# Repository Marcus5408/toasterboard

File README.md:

# Toasterboard

A very scuffed attempt at recreating a Breadboard Companion.

Made for the Hardware workshop led by Acon at [Hack Club Juice](juice.hackclub.com) utilizing a electronics kit from [Hack Club Solder](solder.hackclub.com).

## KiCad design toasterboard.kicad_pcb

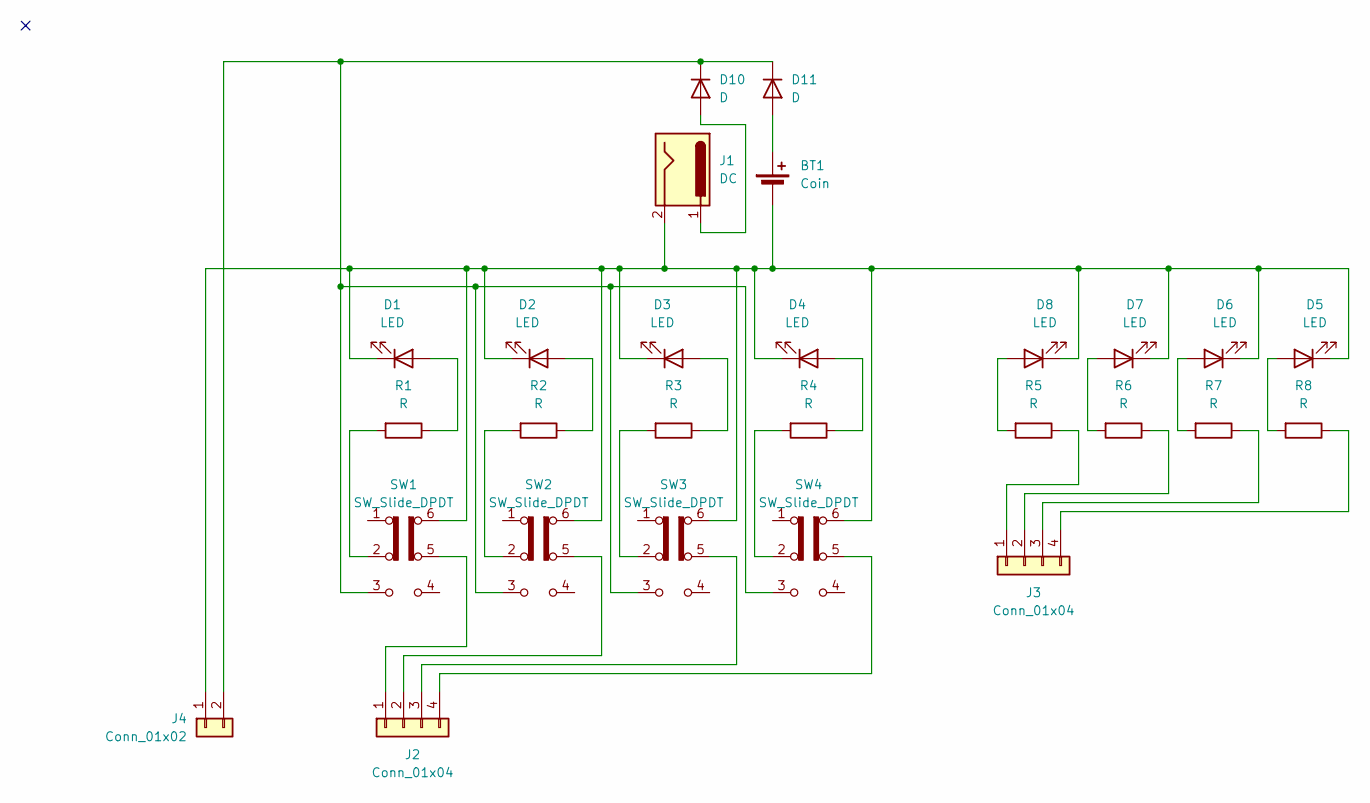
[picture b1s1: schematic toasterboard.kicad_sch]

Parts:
BT1: Coin; BatteryHolder_Keystone_3034_1x20mm
D1, D2, D3, D4, D5, D6, D7, D8: LED; LED_D5.0mm
D10, D11: D; D_DO-35_SOD27_P7.62mm_Horizontal
J1: DC; BarrelJack_CLIFF_FC681465S_SMT_Horizontal
J2, J3: Conn_01x04; PinHeader_1x04_P1.00mm_Vertical
J4: Conn_01x02; PinHeader_1x02_P1.00mm_Vertical
R1, R2, R3, R4, R5, R6, R7, R8: R; R_Axial_DIN0207_L6.3mm_D2.5mm_P7.62mm_Horizontal
SW1, SW2, SW3, SW4: SW_Slide_DPDT; SW_E-Switch_EG1271_SPDT

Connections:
unnamed: BT1.1 (+), D11.2 (A)
unnamed: BT1.2 (-), D1.1 (K), D2.1 (K), D3.1 (K), D4.1 (K), D5.1 (K), D6.1 (K), D7.1 (K), D8.1 (K), J1.2, J4.1, SW1.6 (C), SW2.6 (C), SW3.6 (C), SW4.6 (C)
unnamed: D1.2 (A), R1.1
unnamed: D2.2 (A), R2.1
unnamed: D3.2 (A), R3.1
unnamed: D4.2 (A), R4.1
unnamed: D5.2 (A), R8.2
unnamed: D6.2 (A), R7.2
unnamed: D7.2 (A), R6.2
unnamed: D8.2 (A), R5.2
unnamed: D10.2 (A), J1.1
unnamed: D10.1 (K), D11.1 (K), J4.2, SW1.3 (C), SW2.3 (C), SW3.3 (C), SW4.3 (C)
unnamed: J2.1, SW1.5 (B)
unnamed: J2.2, SW2.5 (B)
unnamed: J2.3, SW3.5 (B)
unnamed: J2.4, SW4.5 (B)
unnamed: J3.1, R5.1
unnamed: J3.2, R6.1
unnamed: J3.3, R7.1
unnamed: J3.4, R8.1
unnamed: R1.2, SW1.2 (B)
unnamed: R2.2, SW2.2 (B)
unnamed: R3.2, SW3.2 (B)
unnamed: R4.2, SW4.2 (B)

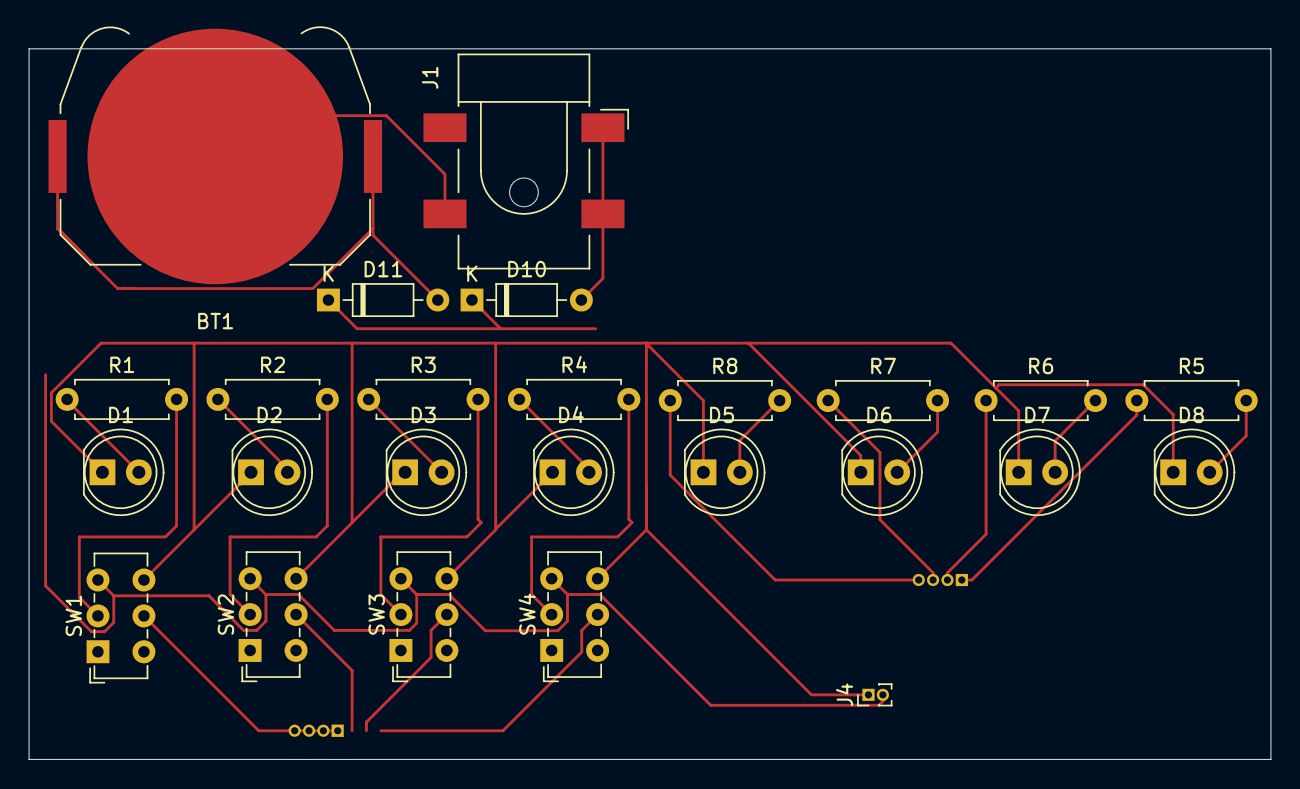
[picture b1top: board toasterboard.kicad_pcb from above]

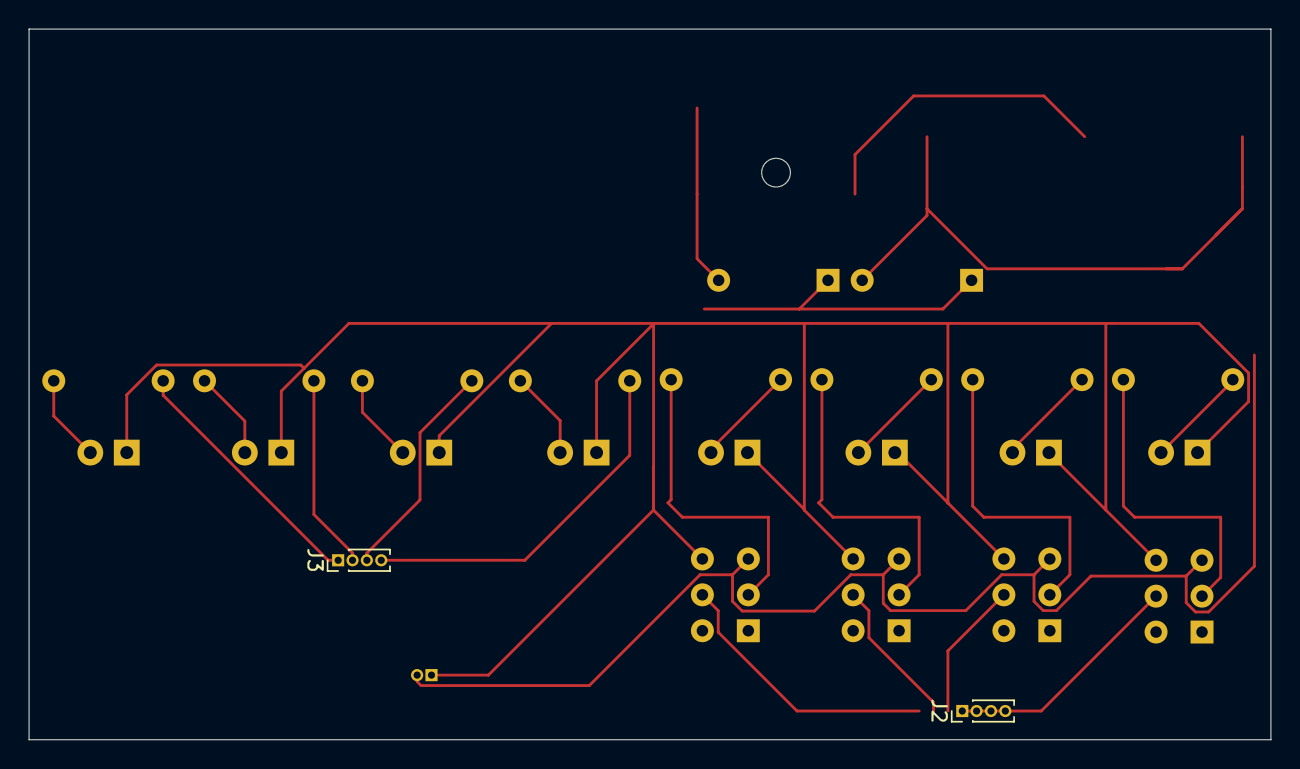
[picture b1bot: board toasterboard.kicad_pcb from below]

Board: 2 copper layers, 86.5 x 49.5 mm, 27 parts (2 on the bottom side), 24 nets.

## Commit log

2025-04-10 init
2025-04-11 feat: add README.md and assets
2025-04-13 fix: change diode footprints, finish connectimg stuff
2025-04-13 feat: clean up, remove second battery
